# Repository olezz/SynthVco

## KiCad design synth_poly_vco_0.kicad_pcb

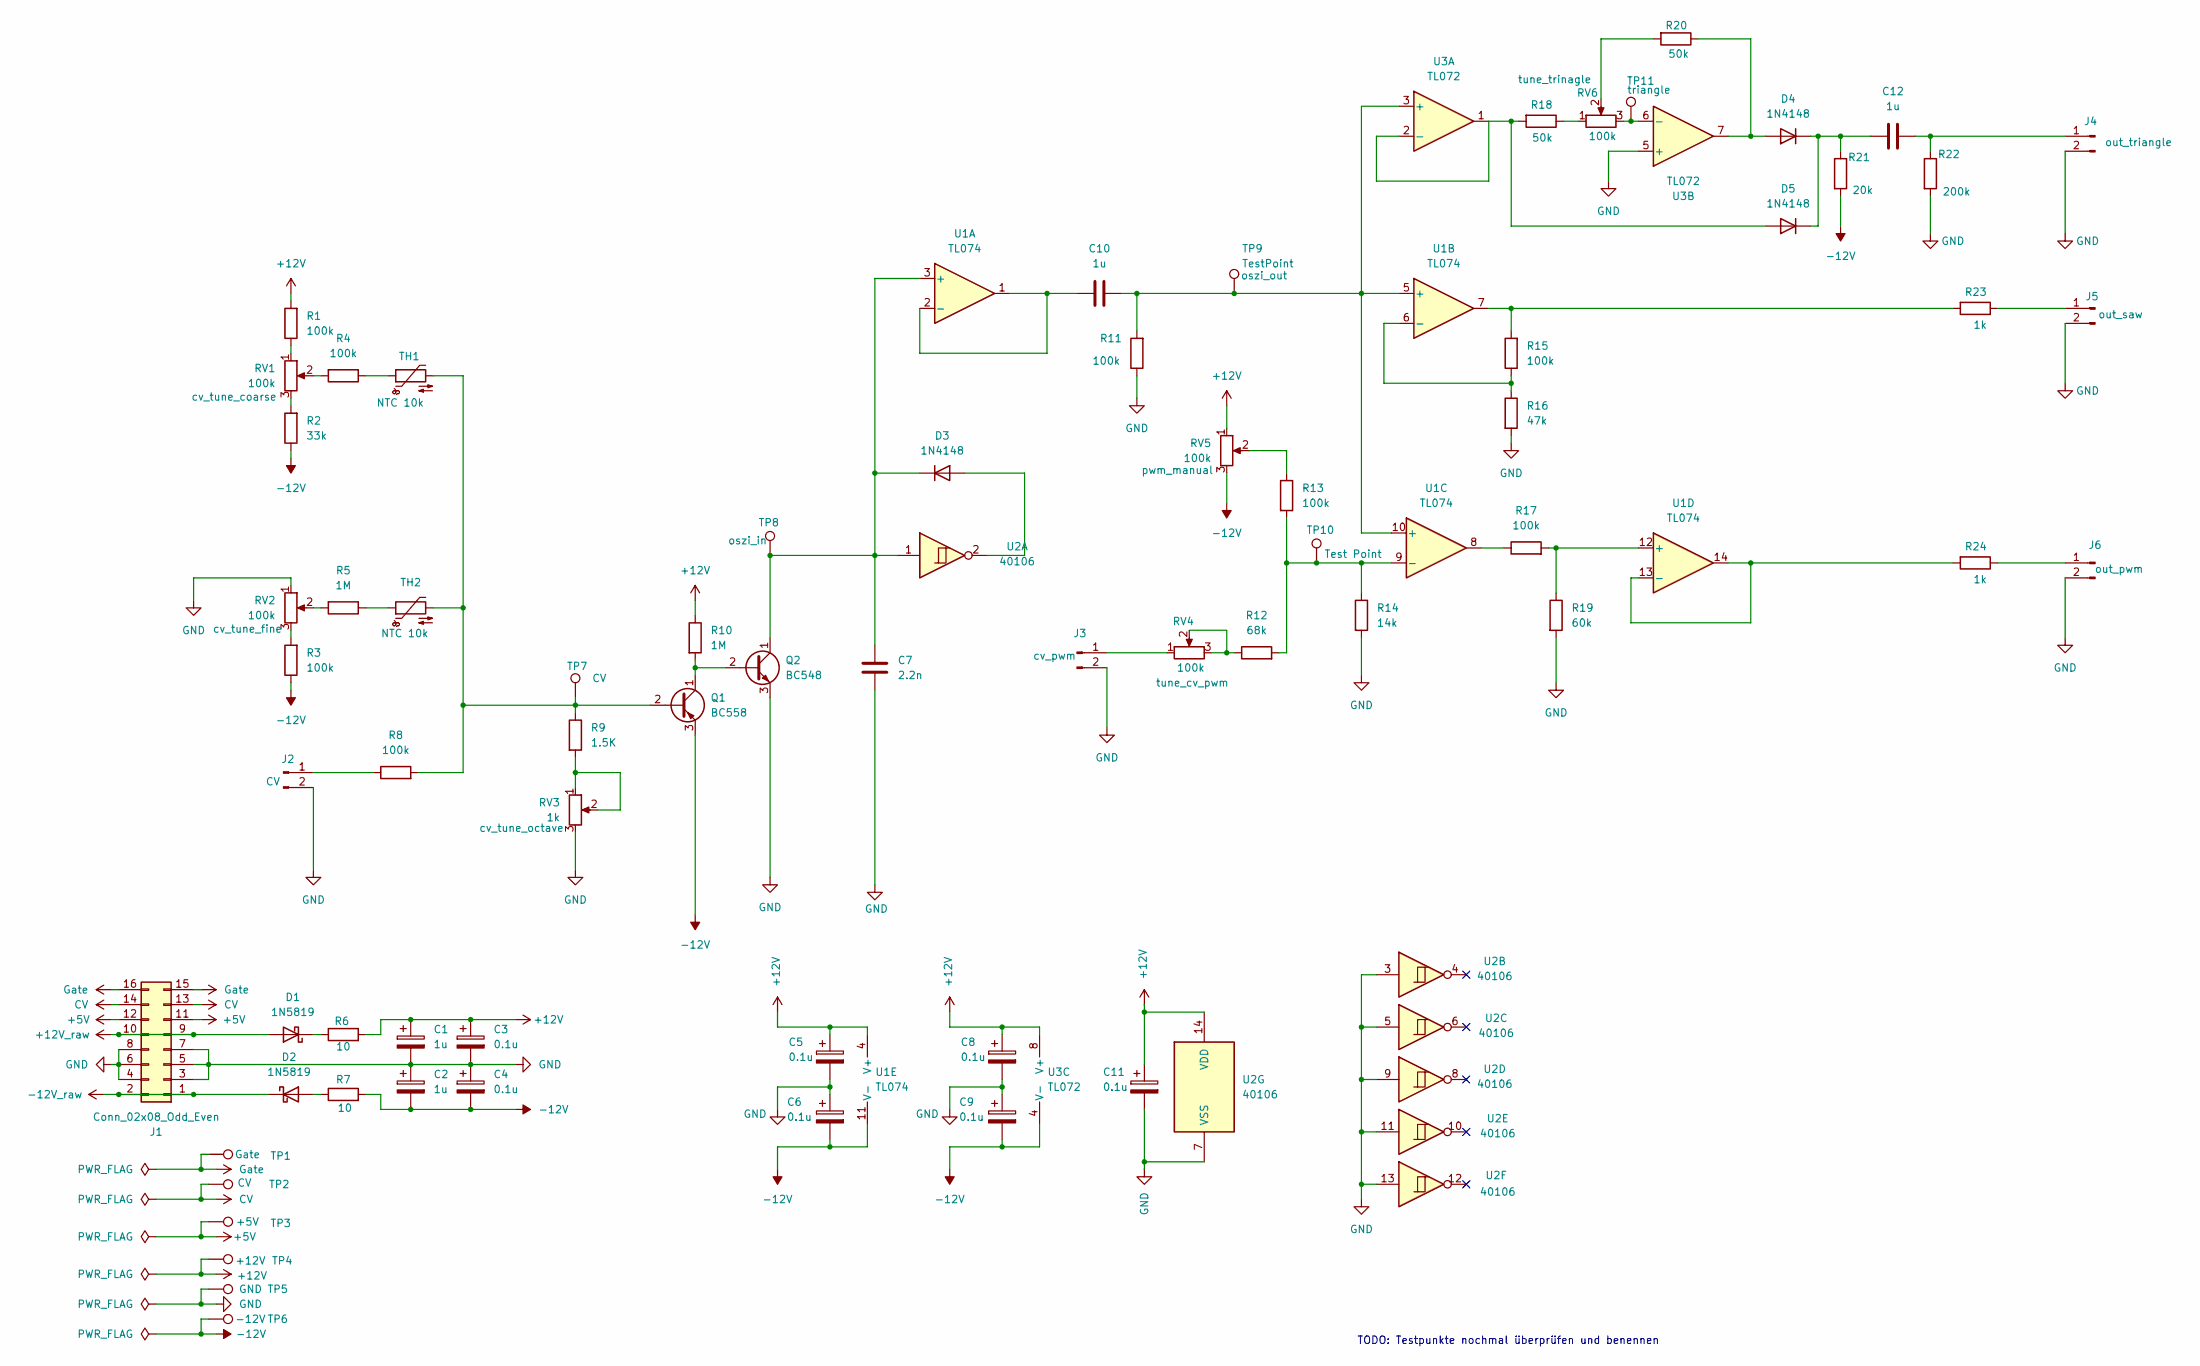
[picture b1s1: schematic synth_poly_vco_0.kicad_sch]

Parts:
C1, C2, C10, C12: 1u; CP_Radial_D6.3mm_P2.50mm
C3, C4, C5, C6, C8, C9, C11: 0.1u; CP_Radial_D6.3mm_P2.50mm
C7: 2.2n; CP_Radial_D6.3mm_P2.50mm
D1, D2: 1N5819; D_DO-41_SOD81_P10.16mm_Horizontal
D3, D4, D5: 1N4148; D_DO-35_SOD27_P7.62mm_Horizontal
J1: Conn_02x08_Odd_Even; IDC-Header_2x08_P2.54mm_Vertical
J2: IN_vco; PinHeader_1x02_P2.54mm_Vertical
J3: Conn_01x02_Pin; PinHeader_1x02_P2.54mm_Vertical
J4: OUT_triangle; PinHeader_1x02_P2.54mm_Vertical
J5: OUT_saw; PinHeader_1x02_P2.54mm_Vertical
J6: OUT_pwm; PinHeader_1x02_P2.54mm_Vertical
Q1: BC558; TO-92_Inline
Q2: BC548; TO-92_Inline
R1, R3, R4, R8, R11, R13, R15, R17: 100k; R_Axial_DIN0204_L3.6mm_D1.6mm_P7.62mm_Horizontal
R2: 33k; R_Axial_DIN0204_L3.6mm_D1.6mm_P7.62mm_Horizontal
R5, R10: 1M; R_Axial_DIN0204_L3.6mm_D1.6mm_P7.62mm_Horizontal
R6, R7: 10; R_Axial_DIN0204_L3.6mm_D1.6mm_P7.62mm_Horizontal
R9: 1.5K; R_Axial_DIN0204_L3.6mm_D1.6mm_P7.62mm_Horizontal
R12: 68k; R_Axial_DIN0204_L3.6mm_D1.6mm_P7.62mm_Horizontal
R14: 14k; R_Axial_DIN0204_L3.6mm_D1.6mm_P7.62mm_Horizontal
R16: 47k; R_Axial_DIN0204_L3.6mm_D1.6mm_P7.62mm_Horizontal
R18, R20: 50k; R_Axial_DIN0204_L3.6mm_D1.6mm_P7.62mm_Horizontal
R19: 60k; R_Axial_DIN0204_L3.6mm_D1.6mm_P7.62mm_Horizontal
R21: 20k; R_Axial_DIN0204_L3.6mm_D1.6mm_P7.62mm_Horizontal
R22: 200k; R_Axial_DIN0204_L3.6mm_D1.6mm_P7.62mm_Horizontal
R23, R24: 1k; R_Axial_DIN0204_L3.6mm_D1.6mm_P7.62mm_Horizontal
RV1, RV2, RV4, RV5, RV6: 100k; Potentiometer_Bourns_3266Y_Vertical
RV3: 1k; Potentiometer_Bourns_3266Y_Vertical
TH1, TH2: NTC 10k; R_Axial_DIN0204_L3.6mm_D1.6mm_P2.54mm_Vertical
TP1, TP2, TP3, TP4, TP5, TP6, TP7, TP10, TP11: Test Point; TestPoint_Pad_D1.5mm
TP8, TP9: TestPoint; TestPoint_Pad_D1.5mm
U1: TL074; DIP-14_W7.62mm_Socket
U2: 40106; DIP-14_W7.62mm_Socket
U3: TL072; DIP-8_W7.62mm_Socket

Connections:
+5V: J1.11, J1.12, TP3.1
+12V: C1.1, C3.1, C5.1, C8.1, C11.1, R1.2, R6.2, R10.1, RV5.1, TP4.1, U1.4 (V+), U2.14 (VDD), U3.8 (V+)
+12V_raw: D1.2 (A), J1.9, J1.10
-12V: C2.2, C4.2, C6.2, C9.2, Q1.3 (E), R2.1, R3.1, R7.2, R21.2, RV5.3, TP6.1, U1.11 (V-), U3.4 (V-)
-12V_raw: D2.1 (K), J1.1, J1.2
CV: J1.13, J1.14, TP2.1
GND: C1.2, C2.1, C3.2, C4.1, C5.2, C6.1, C7.2, C8.2, C9.1, C11.2, J1.3, J1.4, J1.5, J1.6, J1.7, J1.8, J2.2, J3.2, J4.2, J5.2, J6.2, Q2.3 (E), R11.1, R14.2, R16.2, R19.2, R22.2, RV2.1, RV3.3, TP5.1, U2.3, U2.5, U2.7 (VSS), U2.9, U2.11, U2.13, U3.5 (+)
Gate: J1.15, J1.16, TP1.1
unnamed: D1.1 (K), R6.1
unnamed: D2.2 (A), R7.1
unnamed: D3.2 (A), U2.2
unnamed: C7.1, D3.1 (K), Q2.1 (C), TP8.1, U1.3 (+), U2.1
unnamed: D4.2 (A), R20.1, U3.7
unnamed: C12.1, D4.1 (K), D5.1 (K), R21.1
unnamed: D5.2 (A), R18.2, U3.1, U3.2 (-)
unnamed: J2.1, R8.1
unnamed: J3.1, RV4.1
unnamed: C12.2, J4.1, R22.1
unnamed: J5.1, R23.1
unnamed: J6.1, R24.1
unnamed: Q1.2 (B), R8.2, R9.1, TH1.2, TH2.2, TP7.1
unnamed: Q1.1 (C), Q2.2 (B), R10.2
unnamed: R1.1, RV1.1
unnamed: R2.2, RV1.3
unnamed: R3.2, RV2.3
unnamed: R4.1, TH1.1
unnamed: R4.2, RV1.2
unnamed: R5.1, TH2.1
unnamed: R5.2, RV2.2
unnamed: R9.2, RV3.1, RV3.2
unnamed: R12.1, RV4.2, RV4.3
unnamed: R13.1, RV5.2
unnamed: R15.2, R23.2, U1.7
unnamed: R17.1, U1.8
unnamed: R18.1, RV6.1
unnamed: R20.2, RV6.2
unnamed: C10.1, U1.1, U1.2 (-)
unnamed: C10.2, R11.2, TP9.1, U1.5 (+), U1.10 (+), U3.3 (+)
unnamed: R15.1, R16.1, U1.6 (-)
unnamed: R12.2, R13.2, R14.1, TP10.1, U1.9 (-)
unnamed: R17.2, R19.1, U1.12 (+)
unnamed: R24.2, U1.13 (-), U1.14
unnamed: RV6.3, TP11.1, U3.6 (-)

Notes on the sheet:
TODO: Testpunkte nochmal überprüfen und benennen

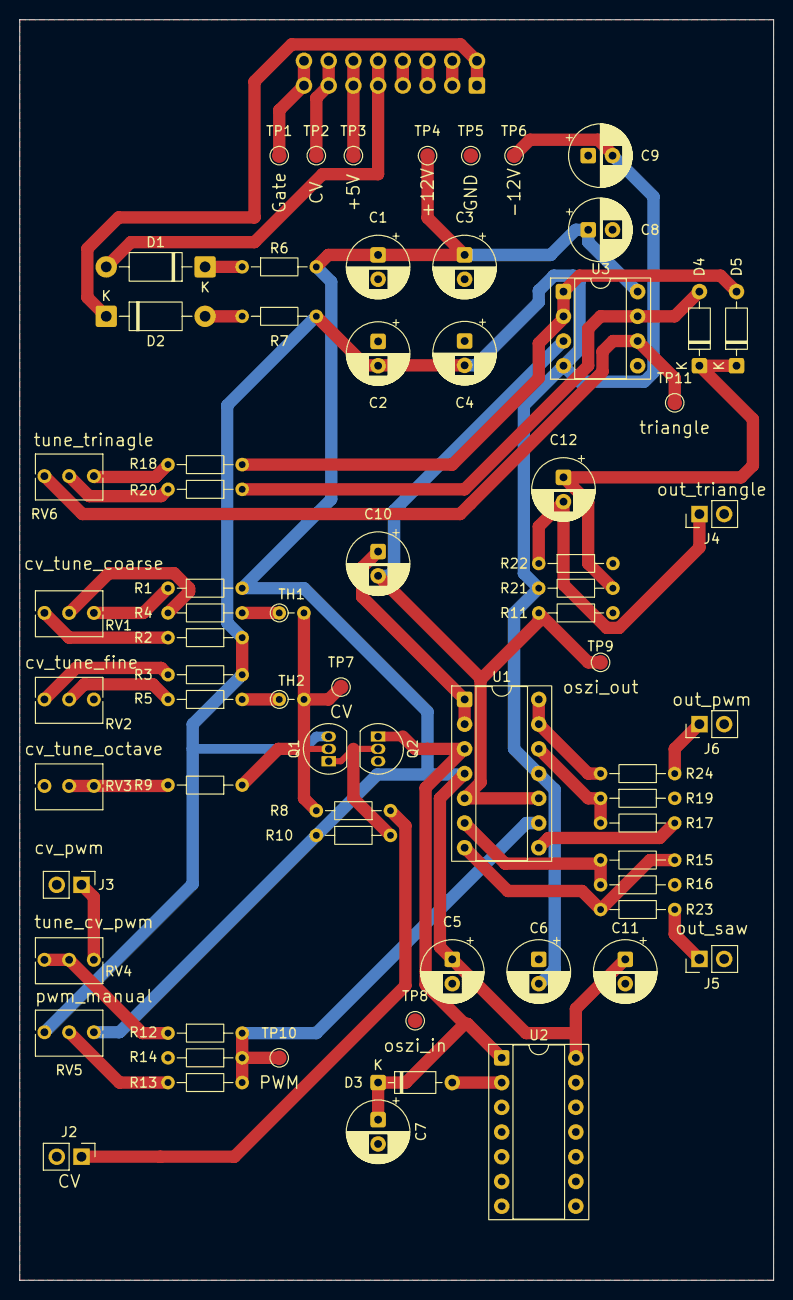
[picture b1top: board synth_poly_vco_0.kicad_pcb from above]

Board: 2 copper layers, 77.5 x 129.5 mm, 71 parts (1 on the bottom side), 43 nets.

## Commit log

2026-01-16 initial commit
2026-01-16 update TL074 and ST power supply
2026-01-16 update power flags
2026-01-26 add triangle output
2026-01-26 Add - power supply filtering - reverse voltage protection - test points
2026-01-26 assigned footprints
2026-01-26 pcb layout
2026-01-29 modify icd optimized paths add descriptions to in and outputs
